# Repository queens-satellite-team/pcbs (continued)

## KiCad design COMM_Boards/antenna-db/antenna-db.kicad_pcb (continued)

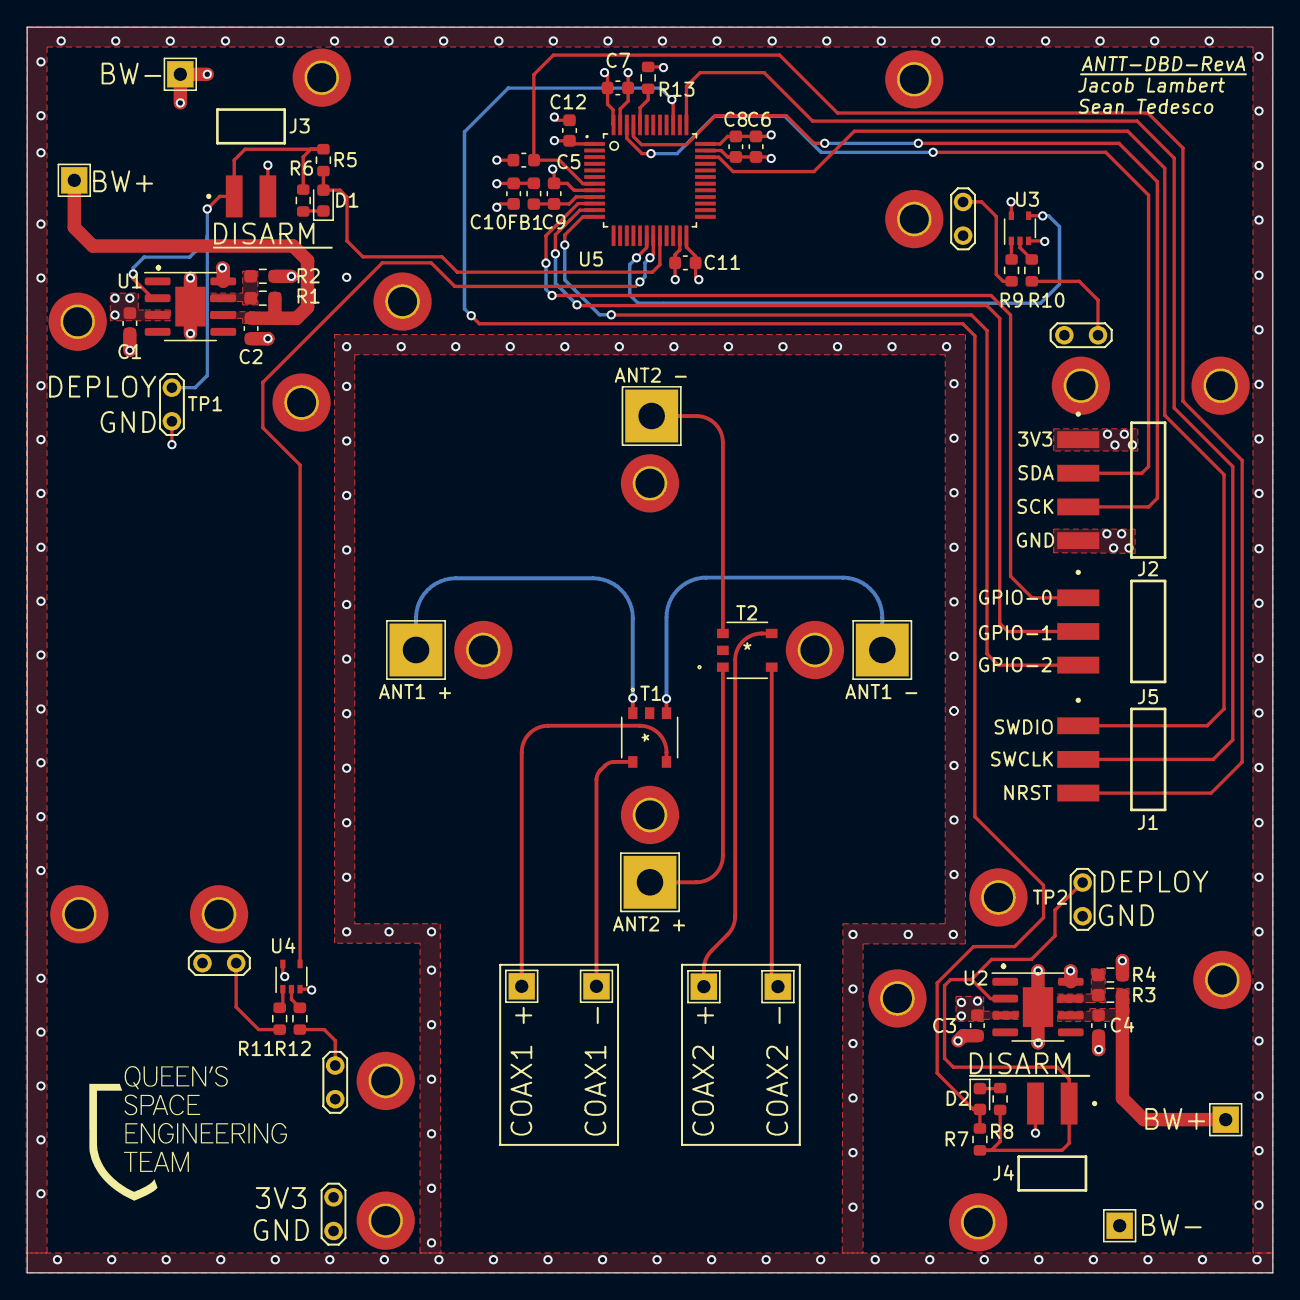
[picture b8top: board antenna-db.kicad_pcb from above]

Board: 4 copper layers, 94.0 x 94.0 mm, 79 parts (0 on the bottom side), 40 nets.

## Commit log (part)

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2019-09-28 Add files via upload
    Battery Pack PCB
2020-07-23 Move transceiver-board repo into here
2020-11-01 OBC PCBs
2020-11-01 STM32 Breakout Board
2021-10-18 Set up OBC board for the 2021-2022 school year
2021-10-26 Add boxes for each sub-project to add their circuitry.
2021-10-28 Add connector to public library
2021-10-30 Add new microcontroller - STM32L4R5ZIT6P
    Old microcontroller is still there, just kept off to the left to review
    the pin definitions of the old one.
2021-11-15 Add new microcontroller that will be used. Add footprint and symbol for common resistors and capacitors Add VREF circuitry, VDDIO and VDDUSB circuit:wq
2021-11-18 dd minor circuitry
2021-11-19 Add IR4301 to schematic
2021-11-25 Added power monitor to circuit
    Added 8-pin max4372F (amplifies by 50 times) with corresponding footnote and current sensing resistor. Out voltage should have 0.3-3.0 V range
2021-11-29 Add footprints for the power monitor circuit
2021-11-29 Create 5V to 3V3
2021-11-29 Create pretty
2021-12-01 MRAM was added Footprint in library footprint, and symbol called MRAM_Symbol
2021-12-02 MRAM symbol added
2021-12-02 MRAM footprint added
2021-12-02 Fix footprint issue with MRAM
2021-12-03 add temperature sensor library to schematic
2022-01-03 Add clock circuitry and power circuitry. Add footprints for devices that did not have any. Add ferrite beads as inputs to each power source for each circuit
2022-01-03 Update cache file
2022-01-14 Add many different circuit elements including connectors and some other passive elements
2022-01-14 Add connections for the 40 pin connector
2022-01-20 Made some final changes to the schematic. Create the location of each of the mounting holes as well as the location of key connectors.
2022-01-21 Change location of board connectors to match ADCS board
2022-01-21 updated RTC capacitor values.
2022-01-23 First layout commit
2022-01-24 Started tracing
    Added traces with J7 and J6 connectors to STM32. Connected power circuit.
2022-01-28 Small change
2022-01-29 Added traces to the bottom of the board
    Added traces to card reader, clock and temperature sensor. Improved traces of J1. Still need to figure out trace widths of high voltage/current traces
2022-01-31 Still some connectionsleft
2022-02-04 Added gf123-0054 (switch) footprint and symbol
2022-02-06 Moved USB connector up
2022-02-08 Add all old footprints to new schematic Add usb input with usb-uart interfacing to provide manual commands using uart
2022-02-08 Minor changes to schematic to make it more readable
2022-02-09 Add pdf version of the schematic
2022-02-09 Layout Adjustments
2022-02-10 Added more traces (hopefully last of them)
2022-02-11 Fix all clearance, silkscreen and trace errors. Partially fixed 3.3V traces
2022-02-11 Continue to work on power distribution within the board
2022-02-11 Fix all remaining errors and redesign power distribution on the board
2022-02-11 Fix one area of ground plane flooding
2022-02-13 Completed final PCB layout changes. Added Gerber files and PDF versions of schematic and layout.
    ***********THIS IS OBC VERSION 1 FINAL*************
2022-02-28 Add photos of physical pcb front and backside
2022-03-04 Add screenshot of the layout
2022-07-27 templates: pc104: include initial support for base template
2022-07-29 templates: pc104: complete template with MH, PC104, and edges
2022-07-29 payload: use PC104 template
2022-07-29 obc: stm32 breakout: remove redundant saves
2022-09-18 Added OBC-DB
2022-10-12 Blocking
2022-10-13 Added a current monitor
2022-11-05 pbc daughterboard: pc104: change schematic
2022-11-09 working on pinout
2022-11-10 Added MCP3008 to convert current monitor analog to serial for pi
2022-11-11 updates to schematic
2022-11-12 obc: daughterboard: redo signal flags on pc104 bus connector
2022-11-12 obc: daughterboard: clean up rtc section using hierarchical sheet
2022-11-12 obc: daughterboard: clean up microsd card section using hierarchical sheet
2022-11-12 obc: daughterboard: include power monitor schematic
2022-11-12 temp sensor footprint
2022-11-12 Fixed libraries path for current monitor in OBC DB
2022-11-12 Updated current monitor resistor to 20mOhms
2022-11-13 hierarchechal sheets
2022-11-14 obc: daughterboard: clean up all schematics for easier reworks
2022-11-14 footprint fix
2022-11-21 adding charging circuit
2022-11-21 adding cutouts
2022-11-22 add buzzer footprint
2022-11-23 Added most wirings, such as pc104 to raspberry, i2c , RTC, temp sensor
    Still need to figure out if our power circuit works before wiring
2022-11-24 Add debug kiCAD
    still a work in progress
2022-11-24 dev of debug schematic
2022-11-26 Adding data traces
2022-12-06 Updated RW and MCU PCBS. Layouts are complete, just need to do routing. (Pushed for Yasin Shahrami)
2022-12-06 Renamed folders to match descriptions in readme
2022-12-16 Create PC104_BreakoutBoard
2022-12-17 Layout completed
2022-12-17 templates: pc104: add step file for 3d viewer
2022-12-17 schematics of smd - also to test saving
2022-12-17 comm-rfb: create project from template
2022-12-17 comm-rfb: reformat for rebase
2022-12-17 power amp schematic
2022-12-17 initial routing done ~ fix bug still
2022-12-17 made PA smaller, added some missing GND connections, and connect AMP-ENABLE
2022-12-17 comm-rfb: reformat main schematic page
2022-12-17 added voltage converter schematic
2022-12-17 libraries: include STM32 and temp sensor for comms
2022-12-17 sma schematics
2022-12-17 comm-rfb: reduce number of sheets in schematic
2022-12-17 possible layout -no connections
2022-12-17 started current and voltage converter
2022-12-17 updated voltage converter
2022-12-17 added current monitor
2022-12-17 added mcu connections
2022-12-18 obc: daughterboard: remove duplicate symbols and footprints
2022-12-18 template: pc104: change hole size and fix pin labels
2022-12-18 obc: db: make daughterboard its own project
2022-12-18 Created Debug PCB
2022-12-19 adcs: updated reaction wheel board from Yasin
2022-12-21 obc: obc-db: generate manufacturing files
2022-12-28 comm-rfb: include correct spacing for cc1120-em connectors, remove traces
2023-01-02 OBC: obc-db: remove more .DS_Store files
2023-01-02 new microSD connector
2023-01-02 OBC: obc-db: remove redundant .DS_Store files
2023-01-02 OBC: obc-db: remove mac fi ''
2023-01-03 comm-rfb: finish connections from MCU
2023-01-03 comm-rfb: finish RF front end
2023-01-03 comm-rfb: generate manufacturing files
2023-01-05 COMM: comm-rfb: remake manufacturing files
2023-01-05 ADCS: rename folders to match board names
2023-01-06 adcs: cleanup unused files
2023-01-09 OBC: umb-db: generate manufacturing files for ordering
2023-02-17 adcs: udpated rwl-db and adcs-ctl on behalf of Yasin
2023-02-19 Updated board to final design
2023-02-20 Update adcs-ctl for yasin
2023-02-21 adcs: added circuit sections to the adcs-ctl schematic
2023-02-21 Board updated
2023-02-21 adcs: mtr-db: updated design from Liam
2023-02-21 adcs: mtr-db: forgot a file oops
2023-02-22 adcs: adcs-ctl: continued silkscreen changes
2023-02-23 adcs: ptd-db: added silksreens
2023-02-23 adcs: ptd-db: deleted floating silkscreen
2023-02-24 adcs: mtr-db: clean up schematic, include status LEDs in schematic
2023-02-24 adcs: mtr-db: fixed back of PCB and updated silkscreen
2023-03-13 adcs: rwl-db: updated 5k resistors to use 0402
2023-03-13 qset-libraries: all: migrate ADCS footprints and schematics
2023-03-13 adcs: rwl-db: change rwl connector to vertical type
2023-03-13 adcs: rwl-db: finish layout of controllers 1 and 2
2023-03-13 adcs: Updated rw-db with latest PWM filter design and added misc silkscreen
2023-03-13 adcs: rwl-db: clean up schematic
2023-03-13 adcs: rwl-db: move connectors to left and right centre of PCB
2023-03-13 qset-library: step: add reaction wheel connectors and controllers
2023-03-13 adcs: rwl-db: finish layout for controllers 3 and 4
2023-03-15 adcs: adcs-ctl: clean up MCU schematic, add 3V3 led
2023-03-15 adcs: adcs-ctl: finish updating footprints, include GPIOs for PMOD connector
2023-03-15 adcs: adcs-ctl: use AMS1117 regulators
2023-03-15 adcs: adcs-ctl: use re1c002unctl transistors over SparkFun transistors
2023-03-15 adcs: adcs-ctl: finish cleaning up sun sensor schematic
2023-03-15 adcs: adcs-ctl: change all footprints to standard kicad footprints or qset footprints
2023-03-15 qset-lib: all: add transistor symbol, footprint, and step for adcs-ctl board
2023-03-15 adcs: adcs-ctl: partial clean up of sun sensor schematic
2023-03-15 qset-lib: footprints: include adcs-ctl footprints from the adcs folder
2023-03-15 adcs: adcs-ctl: include more silkscreen and generate step file
2023-03-15 adcs: adcs-ctl: finish pcb routing
2023-03-15 adcs: adcs-ctl: WIP: continue with routing and layout
2023-03-15 adcs: adcs-ctl: WIP: begin new layout with updates from schematic
2023-03-15 adcs: adcs-ctl: include BOM for manufacturing
2023-03-15 eps: solar panels: final v1
2023-03-15 eps: readme: include readme with note on kicad 7 requirement
2023-03-15 adcs: adcs-ctl: updated MRAM chip to use correct footprint, minor routing and silkscreen changes.
2023-03-15 Adding MRAM chip to qset footprints
2023-04-13 qset-templates: pc104: remoce old backups
2023-04-13 templates: pc104: remove material around MH locations, include step file for header connector
2023-04-13 libraries: footprints: remove duplicate pc104 connector footprint
2023-04-13 finished pcb for sc4216
2023-04-13 get rid of old files
2023-04-13 added mounting holes
2023-04-13 added temp sensor & porgamming/test connections
2023-04-13 made soic-8 v1
2023-04-13 adp7158
2023-04-13 added baluns to antenna connection part
2023-04-13 made pcb for sc4215 - used sc4216 pad since has same dimensions
2023-04-13 made file for adp7158
2023-04-13 updated burn wire connection
2023-04-13 added regulator circuit from datasheet for 5A
2023-04-13 added regulator symbol ~ not circuit yet
2023-04-13 new file for soic-8
2023-04-13 made pcb for adp7159 - used adp7158 footprint since had same dimensions
2023-04-13 fixed burn wire connections
2023-04-13 soic-8: remove redundant files and MAC only files
2023-04-13 COMMS Boards: move antenna board into comms folder
2023-04-17 COMM: antt-dbd: include disarming pin for testing
2023-04-17 qset-images: include images for selfie-cam board
2023-04-17 PAYLOAD: camm-brd: complete RevA of camera board
2023-04-17 PAYLOAD: camm-brd: include gerbers and drill files
2023-04-19 COMM: antt-dbd: map mounting holes to pcb layout
2023-04-21 include SC4216 regulator
2023-04-24 COMM: antt-dbd: finish deployment detection and arming control
2023-04-24 COMM: antt-dbd: begin layout
2023-05-01 libraries: step: include 3D models for horizontal SMD headers
2023-05-01 finish layout of ANTT-DBD
2023-05-01 COMM: include manufacturing and assembly files
2023-05-04 initial battery board schematic
2023-05-04 folder cleanup and backup restored
2023-05-04 eps: battery board: delete v1
2023-05-04 eps: battery board: updated schematic
2023-05-04 eps: battery board: added current and voltage monitor
2023-05-04 eps: battery board: fixed errors
2023-05-04 eps: battery board: added more to inhibits
2023-05-04 eps: battery board: power control
2023-05-04 eps: battery board: added inhibits
2023-05-04 eps: battery board: added AND gate for power control and cleaned up global labels
2023-05-04 eps: battery board: added temp sensor
2023-05-04 eps: battery board: updated board layout
2023-05-04 eps: battery board: more updates to layout
2023-05-04 eps: battery board: dino pic
2023-05-04 eps: battery board: progress on pcb layout
2023-05-04 eps: battery board: more traces
2023-05-04 eps: battery board: worked on traces
2023-05-04 eps:battery:pcb layout
2023-05-04 eps: battery board: RBF bypass changes
2023-05-04 eps: battery board: design review changes
2023-05-04 eps: battery board: more changes before review
2023-05-04 eps: battery board: second design review changes
2023-05-04 eps: battery board: design review schematic changes
2023-05-04 eps: battery board: more design review changes
2023-05-04 eps: battery board: post-layout review changes
2023-05-04 eps: battery board: update footprints on basic components to 0603
2023-05-04 eps: battery board: include manufacturing and assembly files
2023-05-05 eps: battery board: include updated manufacuring files
2024-10-10 treewide: changes from qset computer
    Not sure if these changes are useful but I'll save them to this branch
    in case.
2024-10-11 Altium: adding converted kicad->altium files
